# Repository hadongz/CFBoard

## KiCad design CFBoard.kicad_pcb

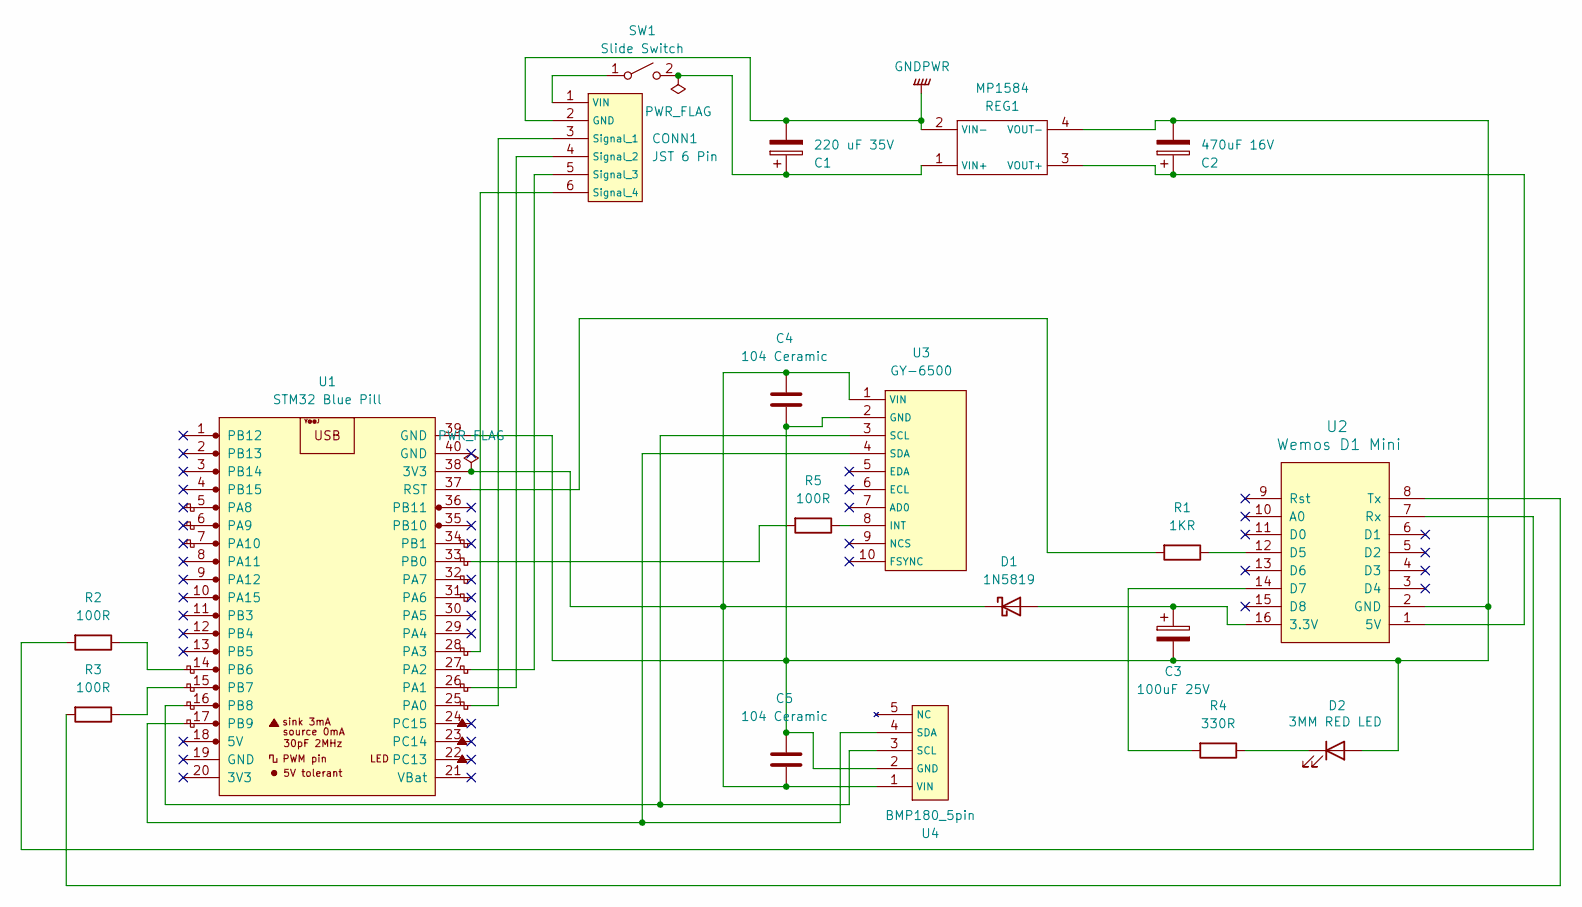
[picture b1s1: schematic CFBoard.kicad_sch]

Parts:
C1: 220 uF 35V; CP_Radial_D6.3mm_P2.50mm
C2: 470uF 16V; CP_Radial_D5.0mm_P2.50mm
C3: 100uF 25V; CP_Radial_D5.0mm_P2.50mm
C4, C5: 104 Ceramic; C_Disc_D4.3mm_W1.9mm_P5.00mm
CONN1: JST 6 Pin; JST_XH_B6B-XH-A_1x06_P2.50mm_Vertical
D1: 1N5819; D_DO-41_SOD81_P10.16mm_Horizontal
D2: 3MM RED LED; LED_D3.0mm
R1: 1KR; R_Axial_DIN0207_L6.3mm_D2.5mm_P7.62mm_Horizontal
R2, R3, R5: 100R; R_Axial_DIN0207_L6.3mm_D2.5mm_P7.62mm_Horizontal
R4: 330R; R_Axial_DIN0207_L6.3mm_D2.5mm_P7.62mm_Horizontal
REG1: MP1584
SW1: Slide Switch; SW_Slide-03_Wuerth-WS-SLTV_10x2.5x6.4_P2.54mm
U1: STM32 Blue Pill; YAAJ_BluePill_2
U2: Wemos D1 Mini; D1_mini_board
U3: GY-6500; GY6500
U4: BMP180_5pin; BMP180_5Pin

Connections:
GNDPWR: C1.2, CONN1.2 (GND), REG1.2 (VIN-)
unnamed: CONN1.3 (Signal_1), U1.25 (PA0)
unnamed: CONN1.4 (Signal_2), U1.26 (PA1)
unnamed: CONN1.5 (Signal_3), U1.27 (PA2)
unnamed: CONN1.6 (Signal_4), U1.28 (PA3)
unnamed: CONN1.1 (VIN), SW1.1 (A)
unnamed: C3.1, D1.2 (A), U2.16 (3.3V)
unnamed: C4.1, C5.2, D1.1 (K), U1.38 (3V3), U3.1 (VIN), U4.1 (VIN)
unnamed: C2.2, C3.2, C4.2, C5.1, D2.2 (A), REG1.4 (VOUT-), U1.39 (GND), U2.2 (GND), U3.2 (GND), U4.2 (GND)
unnamed: D2.1 (K), R4.1
unnamed: C1.1, REG1.1 (VIN+), SW1.2 (B)
unnamed: C2.1, REG1.3 (VOUT+), U2.1 (5V)
unnamed: R5.2, U1.33 (PB0)
unnamed: R2.1, U1.14 (PB6)
unnamed: R3.1, U1.15 (PB7)
unnamed: U1.16 (PB8), U3.3 (SCL), U4.3 (SCL)
unnamed: U1.17 (PB9), U3.4 (SDA), U4.4 (SDA)
unnamed: R1.2, U1.37 (RST)
unnamed: R1.1, U2.12 (D5)
unnamed: R4.2, U2.14 (D7)
unnamed: R2.2, U2.7 (Rx)
unnamed: R3.2, U2.8 (Tx)
unnamed: R5.1, U3.8 (INT)

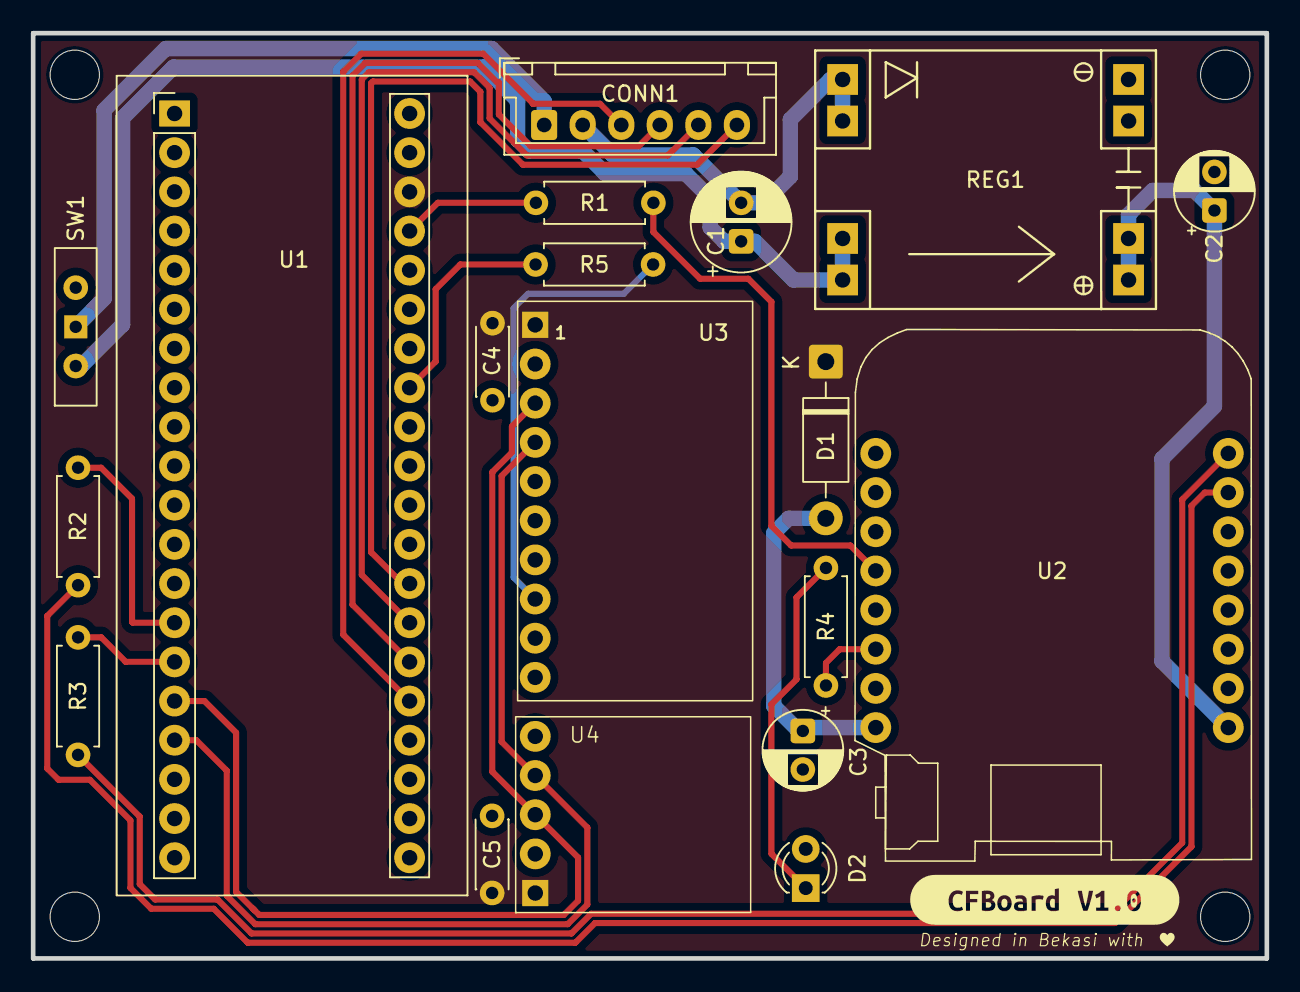
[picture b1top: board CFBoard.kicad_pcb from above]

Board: 2 copper layers, 80.0 x 60.0 mm, 20 parts (0 on the bottom side), 23 nets.

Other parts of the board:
kibuzzard-689068BD: G***; kibuzzard-689068BD

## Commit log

2025-07-09 [initial commit]
2025-07-11 feat: layout all the components
2025-07-11 feat: pcb layout
2025-07-11 feat: wrap up version 1
2025-07-12 chore: fix trace
2025-07-17 feat: add silkscreen name and re-trace
2025-07-17 feat: generate gerbers
2025-07-21 feat: update design
2025-08-04 feat: update jst connector footprint design
